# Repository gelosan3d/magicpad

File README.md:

# Angelos' MagicPad

### Renders + Workplace Screenshots 

---

### Inspiration: 
I got my main inspiration from existing streaming decks and macropads such as the Elgado Streakdeck. I really liked the customisability but always though that the buttons were very tacky when pressed and I didn't particularly like the lack of a knob in some models

### BOM:
- 1x XIAO RP2040
- 2x SK6812MINI-E LED's 
- 2x EC11 Rotary Encoders
- 8x Cherry MX Footprint Switches
- 1x 0.91" OLED Panel
- 1x [MCP23017 IO Expander](https://item.taobao.com/item.htm?id=873700756247) (TaoBao Link)
- 3x [4.7kΩ Resistors](https://detail.tmall.com/item.htm?abbucket=4&id=855810249338&mi_id=0000HXPAmHcXGjU2EkSrUGMlTOs7axLLb7Gr6H2aFVrdahM) (TMall Link) 
- 4x [m3 5W4D Heat-set Inserts](https://www.aliexpress.us/item/2255800046543591.html)
- 4x m3x16mm Screws

#### 3D Print:
  - Top_Case.stl
  - Bottom_Case.stl

Schematic            |  PCB         |   Case
:-------------------------:|:-------------------------:|:-------------------------:|
  |   | 

### Licensing
This project falls under the MIT License (see LICENSE.md), which I chose because of how much I used all the amazing community projects and help (a ***lot*** with the code) and the support from the overall open-source community. 

This has inspired and made me want to leave my work as open source, hopefully inspiring or helping someone else in the future! 

--- 

### Thanks!!!
Many many many thanks to everyone at the Hackclub team and AMD for making this work, really amazing help and support to the whole community!

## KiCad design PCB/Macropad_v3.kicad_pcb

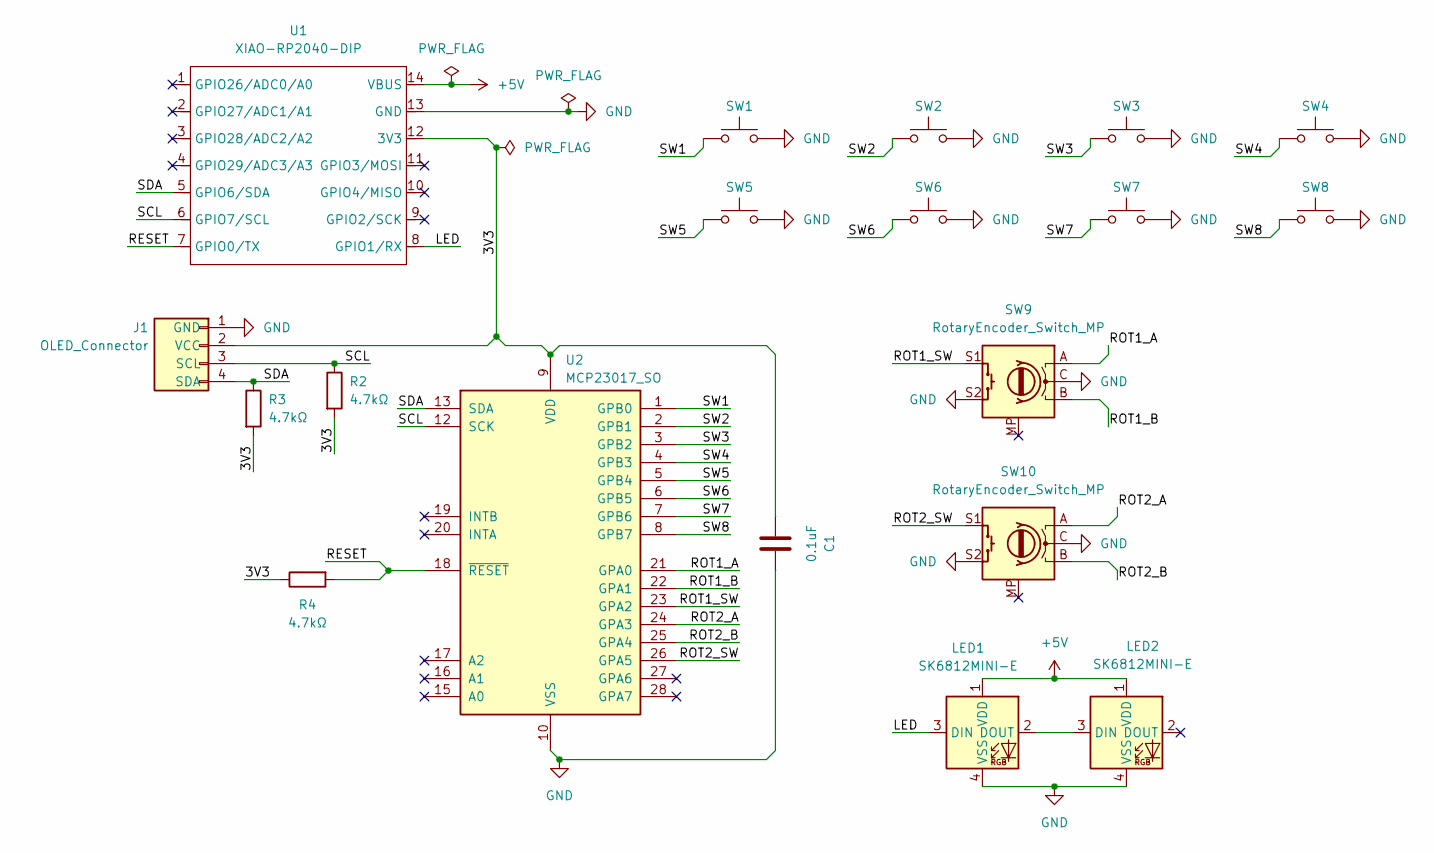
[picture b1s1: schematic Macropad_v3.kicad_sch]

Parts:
C1: 0.1uF; C_0603_1608Metric_Pad1.08x0.95mm_HandSolder
J1: OLED_Connector; SSD1306-0.91-OLED-4pin-128x32
LED1, LED2: SK6812MINI-E; LED_6028R
R2, R3, R4: 4.7kΩ; R_0603_1608Metric_Pad0.98x0.95mm_HandSolder
SW1, SW2, SW3, SW4, SW5, SW6, SW7, SW8: SW_Push; SW_Cherry_MX_1.00u_PCB
SW9, SW10: RotaryEncoder_Switch_MP; RotaryEncoder_Alps_EC11E-Switch_Vertical_H20mm_CircularMoun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
U1: XIAO-RP2040-DIP
U2: MCP23017_SO; SOIC-28W_7.5x17.9mm_P1.27mm

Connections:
+5V: LED1.1 (VDD), LED2.1 (VDD), U1.14 (VBUS)
/3V3: C1.1, J1.2 (VCC), R2.2, R3.2, R4.1, U1.12 (3V3), U2.9 (VDD)
/LED: LED1.3 (DIN), U1.8 (GPIO1/RX)
/RESET: R4.2, U1.7 (GPIO0/TX), U2.18 (~RESET)
/ROT1_A: SW9.A, U2.21 (GPA0)
/ROT1_B: SW9.B, U2.22 (GPA1)
/ROT1_SW: SW9.S1, U2.23 (GPA2)
/ROT2_A: SW10.A, U2.24 (GPA3)
/ROT2_B: SW10.B, U2.25 (GPA4)
/ROT2_SW: SW10.S1, U2.26 (GPA5)
/SCL: J1.3 (SCL), R2.1, U1.6 (GPIO7/SCL), U2.12 (SCK)
/SDA: J1.4 (SDA), R3.1, U1.5 (GPIO6/SDA), U2.13 (SDA)
/SW1: SW1.1, U2.1 (GPB0)
/SW2: SW2.1, U2.2 (GPB1)
/SW3: SW3.1, U2.3 (GPB2)
/SW4: SW4.1, U2.4 (GPB3)
/SW5: SW5.1, U2.5 (GPB4)
/SW6: SW6.1, U2.6 (GPB5)
/SW7: SW7.1, U2.7 (GPB6)
/SW8: SW8.1, U2.8 (GPB7)
GND: C1.2, J1.1 (GND), LED1.4 (VSS), LED2.4 (VSS), SW1.2, SW2.2, SW3.2, SW4.2, SW5.2, SW6.2, SW7.2, SW8.2, SW9.C, SW9.S2, SW10.C, SW10.S2, U1.13 (GND), U2.10 (VSS)
unnamed: LED1.2 (DOUT), LED2.3 (DIN)

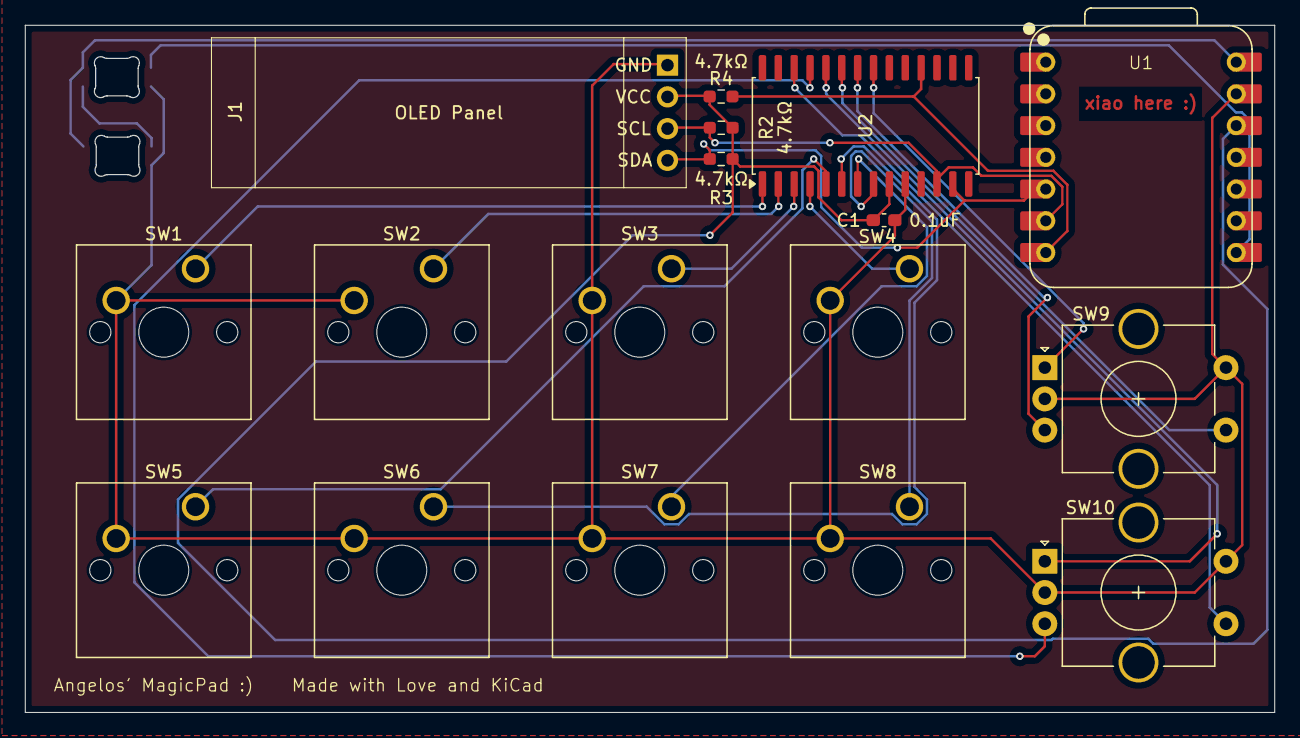
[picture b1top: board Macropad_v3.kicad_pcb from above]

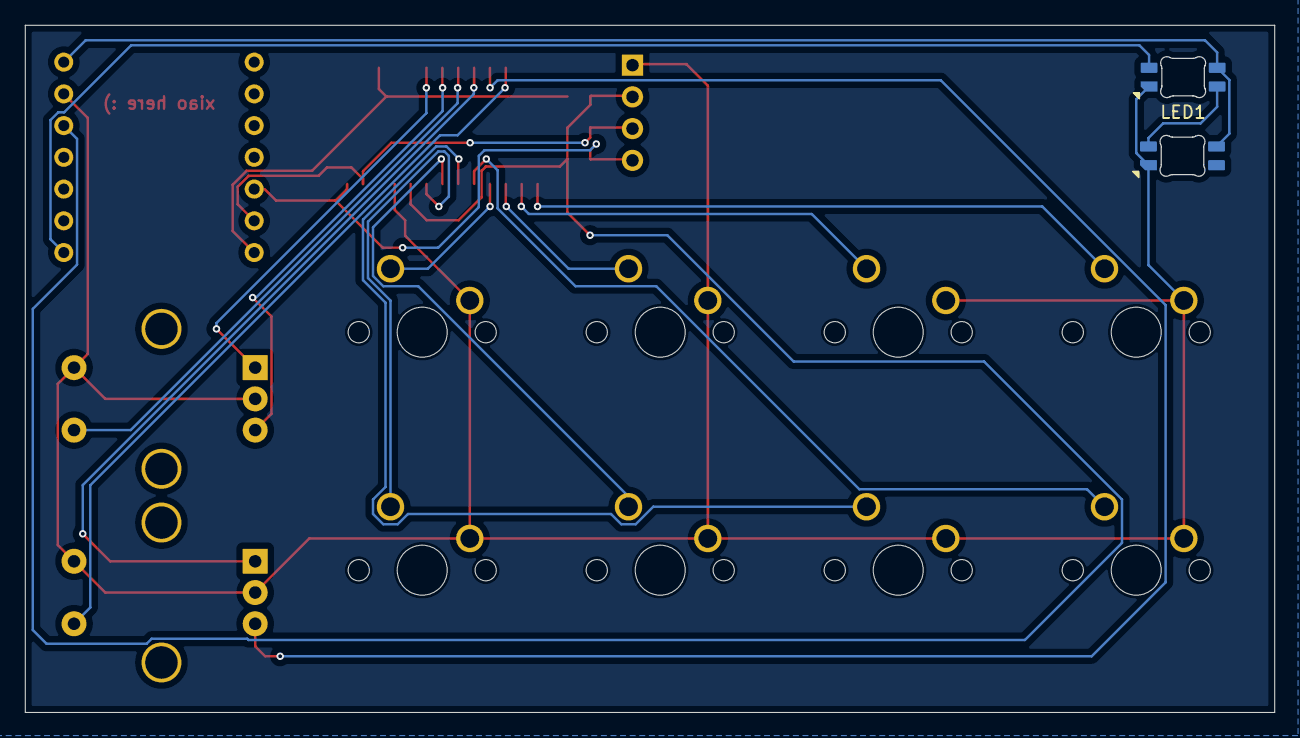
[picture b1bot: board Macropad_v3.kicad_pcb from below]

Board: 2 copper layers, 99.9 x 55.0 mm, 19 parts (2 on the bottom side), 22 nets.

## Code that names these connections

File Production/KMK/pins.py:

# firmware/board/pins.py
# imports pins for both XIAO and MCP23017
import board
import busio
from kmk_firmware.kmk.extensions.ioexpander import MCP23017
from kmk_firmware.kmk.extensions.display.ssd1306 import ssd1306

i2c = busio.I2C(board.SCL, board.SDA)       # I2C bus (XIAO default pins)
expander = MCP23017(i2c, address=0x20)      # MCP23017 at address 0x20
    
# OLED display
oled = SSD1306_I2C(
    128, 
    32, 
    i2c, 
    addr=0x3C
)

"""
K_<number>      - keys
ENC<n>_<signal> - encoders
LED_<name>      - LEDs 
"""

# reset
SYS_RESET = board.GP0 # reset pin

# keys
K_1 = expander.get_pin(8)    # SW1
K_2 = expander.get_pin(9)    # SW2
K_3 = expander.get_pin(10)   # SW3
K_4 = expander.get_pin(11)   # SW4
K_5 = expander.get_pin(12)   # SW5
K_6 = expander.get_pin(13)   # SW6
K_7 = expander.get_pin(14)   # SW7
K_8 = expander.get_pin(15)   # SW8

# encoder
ENC1_A  = expander.get_pin(0)   # ROT1_A
ENC1_B  = expander.get_pin(1)   # ROT1_B
ENC1_SW = expander.get_pin(2)   # ROT1_SW

ENC2_A  = expander.get_pin(3)   # ROT2_A
ENC2_B  = expander.get_pin(4)   # ROT2_B
ENC2_SW = expander.get_pin(5)   # ROT2_SW

"""
from pins import (
    DIRECT_PINS,
    ENC1_A, ENC1_B,
    ENC2_A, ENC2_B,
    LED_DATA,
)"""

ENCODER_PINS = (
    (ENC1_A, ENC1_B),
    (ENC2_A, ENC2_B),
)

DIRECT_PINS = (
    K_1, 
    K_2, 
    K_3, 
    K_4, 
    ENC1_SW,
    K_5, 
    K_6, 
    K_7, 
    K_8, 
    ENC2_SW
)

# LEDs
LED_DATA = board.GP1 # SK6812 MINI

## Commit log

2025-12-22 v1 uploads
    added basic files, still missing files for KMK Firmware, README, LISCENCE, and .gitignore
2025-12-22 added LICENSE.md
2025-12-23 added firmware
    firmware added with into KMK - production, and firmware
2025-12-23 added README.md
2025-12-23 Update README.md
    Added licensing information and acknowledgments to the README.
2025-12-24 Added Case_Pretty_1.png
2025-12-24 updated README.md
    added screenshot of case without electronics
